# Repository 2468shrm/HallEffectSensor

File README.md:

# HallEffectSensor

This is a simple sensor for FRC mechanisms based on the Honeywell SM351LT.
The intended uses include contactless extension/rotation limit sensing.
I've tried many times to get the team to use one on turrets or elevators
and I hope that creating one for the team might encourage their use.

The datasheet for the sensor is [here](https://www.mouser.com/datasheet/2/187/HWSC_S_A0012827053_1-3073404.pdf).

The operating voltage of this circuit is 3.3V. The connector to a connecting
single-board computer is a 3-pin signal/power/ground 0.1 inch header.  It is
3.3V since the sensor operates at 3.3V and there was no intention of including
a 5V-to-3.3V regulator to minimize costs.

Since limit sensing is a digital operation (you're at the limit or not)
the circuit includes a voltage divider to set a sensitivity/reference level
and comparator to digitize the sensing. It also includes a LED to indicate
the output of the sensor.

There are two 3-pin 0.1" header footprints.
- One for the connection to a DIO on a feather board
- One that is in parallel to the output of the sensor, so that the sensor may
be depopulated an another 3.3V sensor is connected externally, OR, it makes a
good probe point

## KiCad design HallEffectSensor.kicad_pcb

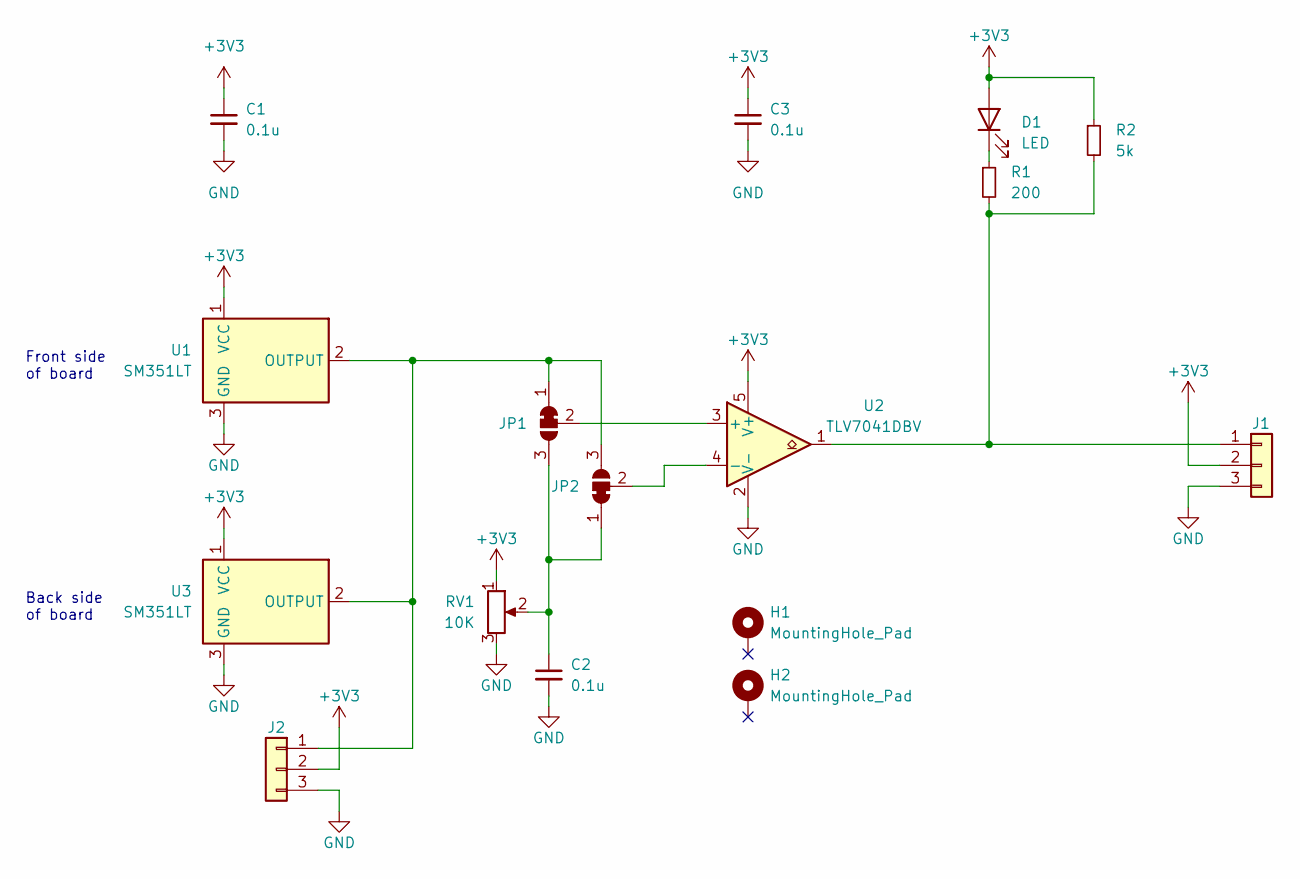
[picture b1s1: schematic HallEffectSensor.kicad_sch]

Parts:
C1, C2, C3: 0.1u; C_0805_2012Metric
D1: LED; LED_1206_3216Metric
H1, H2: MountingHole_Pad; MountingHole_2.2mm_M2_Pad
J1, J2: Conn_01x03; PinHeader_1x03_P2.54mm_Vertical
JP1, JP2: SolderJumper_3_Bridged12; SolderJumper-3_P1.3mm_Bridged12_Pad1.0x1.5mm
R1: 200; R_0805_2012Metric
R2: 5k; R_0805_2012Metric
RV1: 10K; PVG3A
U1, U3: SM351LT; SOT-23
U2: TLV7041DBV; SOT-23-5_HandSoldering

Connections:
+3V3: C1.1, C3.1, D1.2 (A), J1.2, J2.2, R2.1, RV1.1, U1.1 (VCC), U2.5 (V+), U3.1 (VCC)
GND: C1.2, C2.2, C3.2, J1.3, J2.3, RV1.3, U1.3 (GND), U2.2 (V-), U3.3 (GND)
unnamed: C2.1, JP1.3 (B), JP2.1 (A), RV1.2
unnamed: D1.1 (K), R1.1
unnamed: J1.1, R1.2, R2.2, U2.1
unnamed: J2.1, JP1.1 (A), JP2.3 (B), U1.2 (OUTPUT), U3.2 (OUTPUT)
unnamed: JP1.2 (C), U2.3 (+)
unnamed: JP2.2 (C), U2.4 (-)

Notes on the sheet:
Front side of board
Back side of board

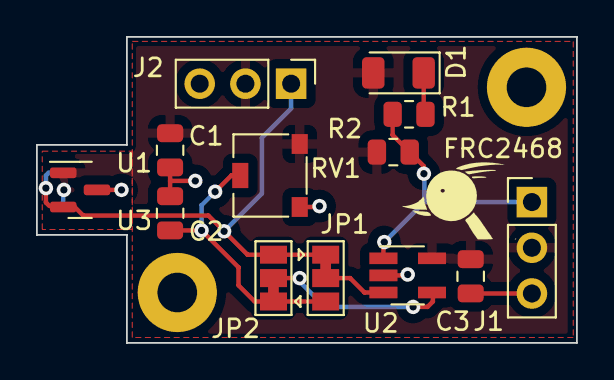
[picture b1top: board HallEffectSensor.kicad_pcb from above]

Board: 2 copper layers, 30.0 x 17.0 mm, 16 parts (1 on the bottom side), 8 nets.

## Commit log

2022-12-20 First commit of schematic and pcb components plus post layout images
2022-12-20 Improved description
